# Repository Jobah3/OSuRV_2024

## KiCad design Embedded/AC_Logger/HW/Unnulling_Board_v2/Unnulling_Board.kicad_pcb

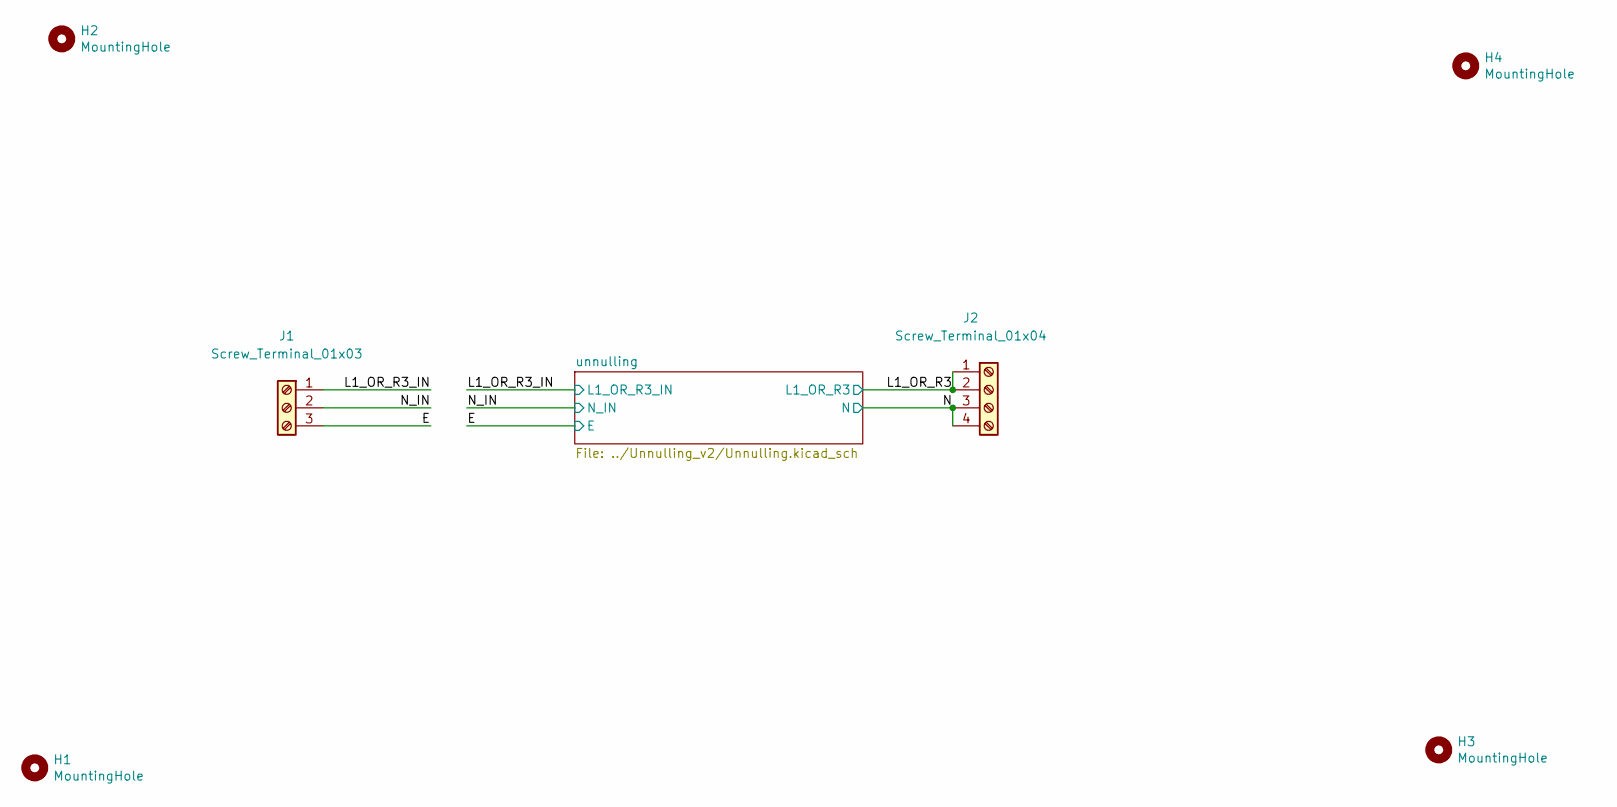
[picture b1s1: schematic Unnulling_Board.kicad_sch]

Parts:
H1, H2, H3, H4: MountingHole; MountingHole_3.2mm_M3_ISO7380_Pad
J1: Screw_Terminal_01x03; TerminalBlock_bornier-3_P5.08mm
J2: Screw_Terminal_01x04; TerminalBlock_bornier-4_P5.08mm

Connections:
/E: J1.3; also elsewhere on the board
/L1_OR_R3: J2.1, J2.2; also elsewhere on the board
/L1_OR_R3_IN: J1.1; also elsewhere on the board
/N: J2.3, J2.4; also elsewhere on the board
/N_IN: J1.2; also elsewhere on the board

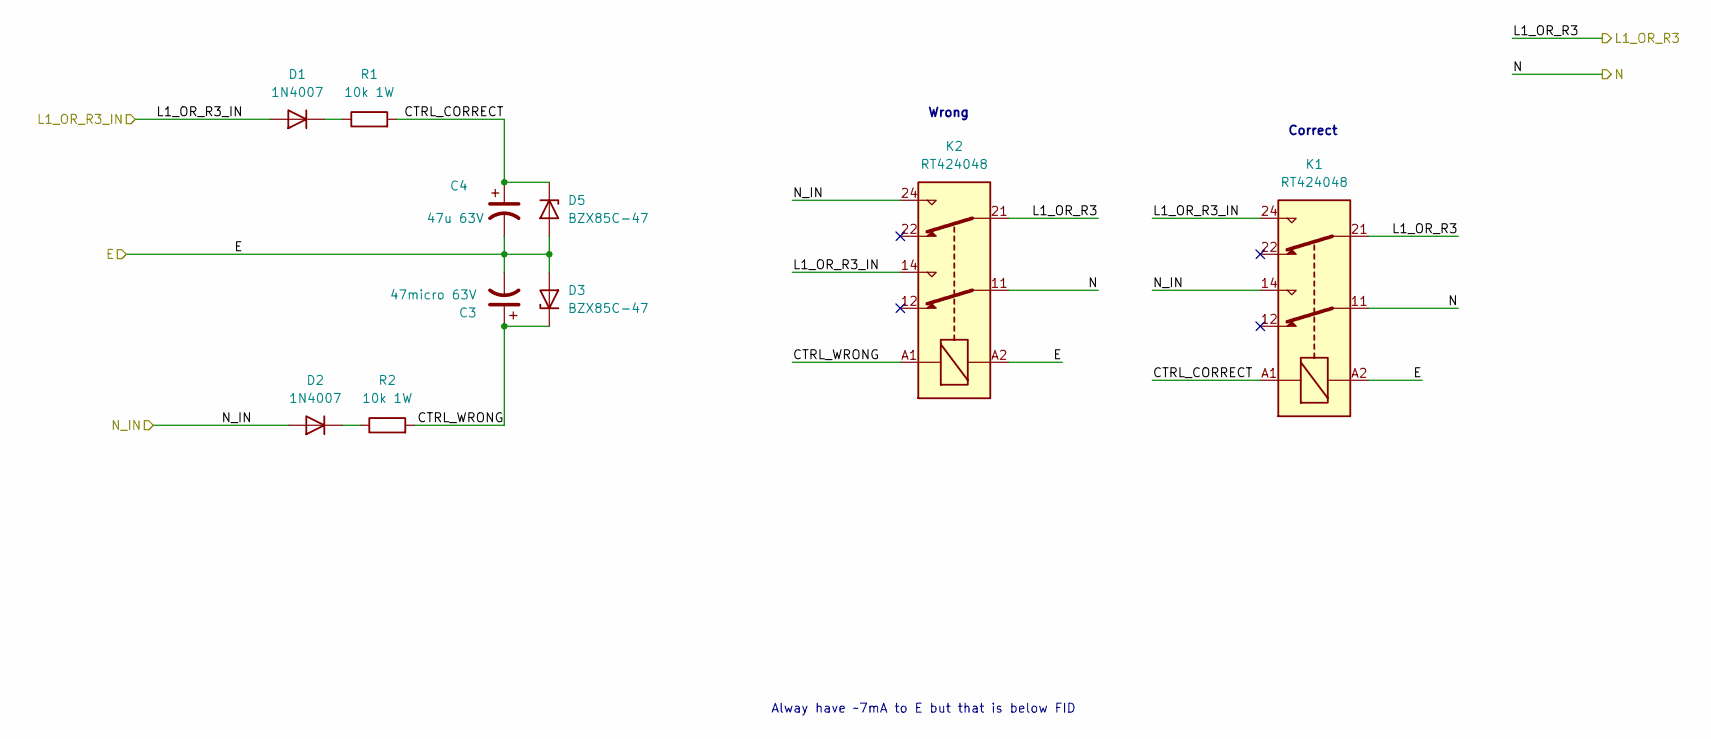
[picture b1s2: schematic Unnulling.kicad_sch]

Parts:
C3: 47micro 63V; CP_Radial_D6.3mm_P2.50mm
C4: 47u 63V; CP_Radial_D6.3mm_P2.50mm
D1, D2: 1N4007; D_DO-35_SOD27_Pinf_Horizontal
D3, D5: BZX85C-47; D_DO-41_SOD81_P2.54mm_Vertical_KathodeUp
K1, K2: RT424048; Relay_DPDT_Schrack-RT2-FormC_RM5mm
R1, R2: 10k 1W; R_Axial_DIN0309_L9.0mm_D3.2mm_P12.70mm_Horizontal

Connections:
/E: C3.2, C4.2, D3.2 (A), D5.2 (A), K1.A2, K2.A2; also elsewhere on the board
/L1_OR_R3: K1.21, K2.21; also elsewhere on the board
/L1_OR_R3_IN: D1.2 (A), K1.24, K2.14; also elsewhere on the board
/N: K1.11, K2.11; also elsewhere on the board
/N_IN: D2.2 (A), K1.14, K2.24; also elsewhere on the board
/unnulling/CTRL_CORRECT: C4.1, D5.1 (K), K1.A1, R1.2
/unnulling/CTRL_WRONG: C3.1, D3.1 (K), K2.A1, R2.2
unnamed: D1.1 (K), R1.1
unnamed: D2.1 (K), R2.1

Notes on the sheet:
Alway have ~7mA to E but that is below FID
Wrong
Correct

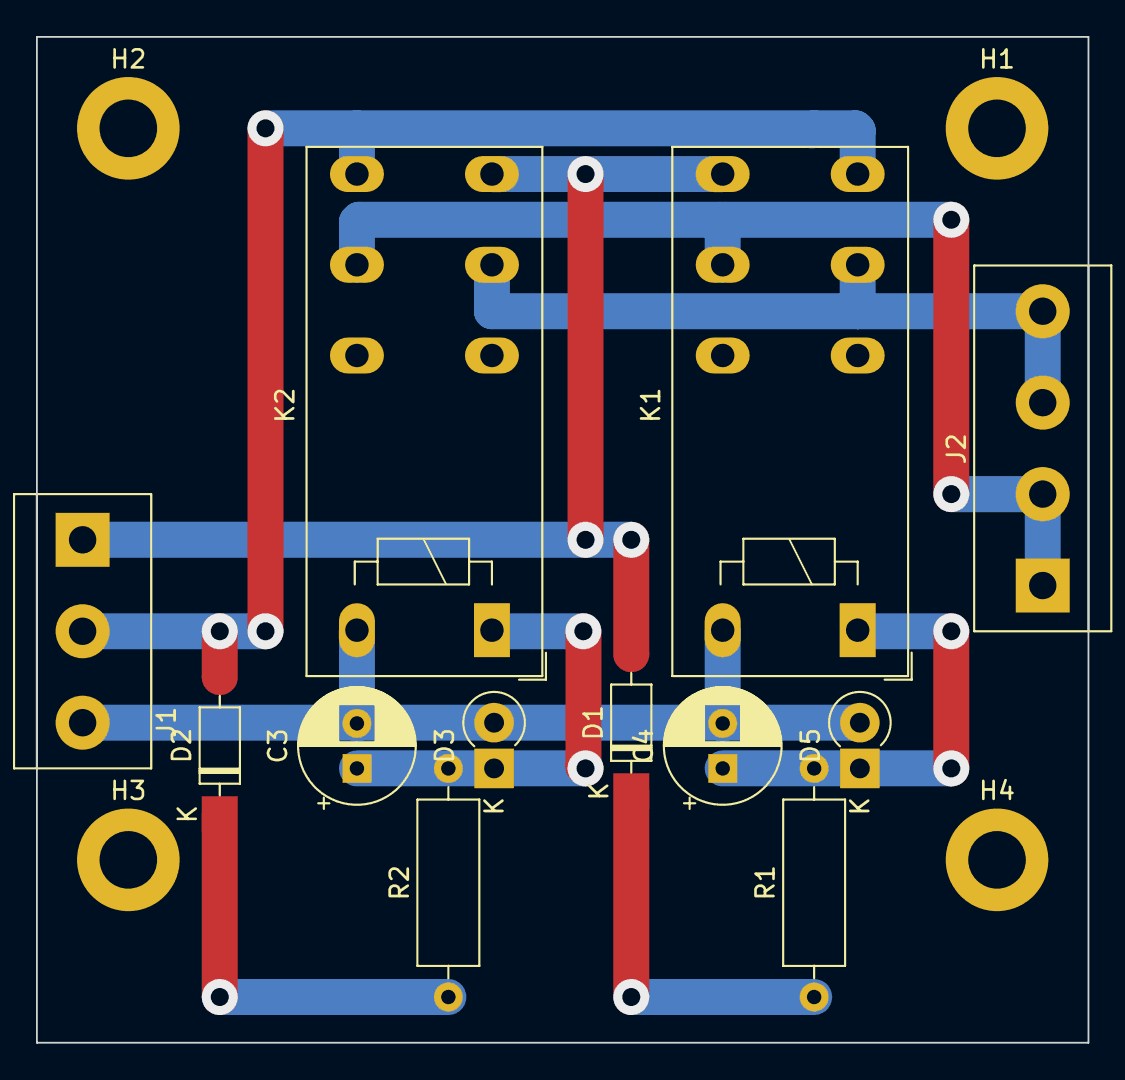
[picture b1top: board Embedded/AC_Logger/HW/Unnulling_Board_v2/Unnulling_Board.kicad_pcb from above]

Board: 2 copper layers, 58.4 x 55.9 mm, 16 parts (0 on the bottom side), 9 nets.

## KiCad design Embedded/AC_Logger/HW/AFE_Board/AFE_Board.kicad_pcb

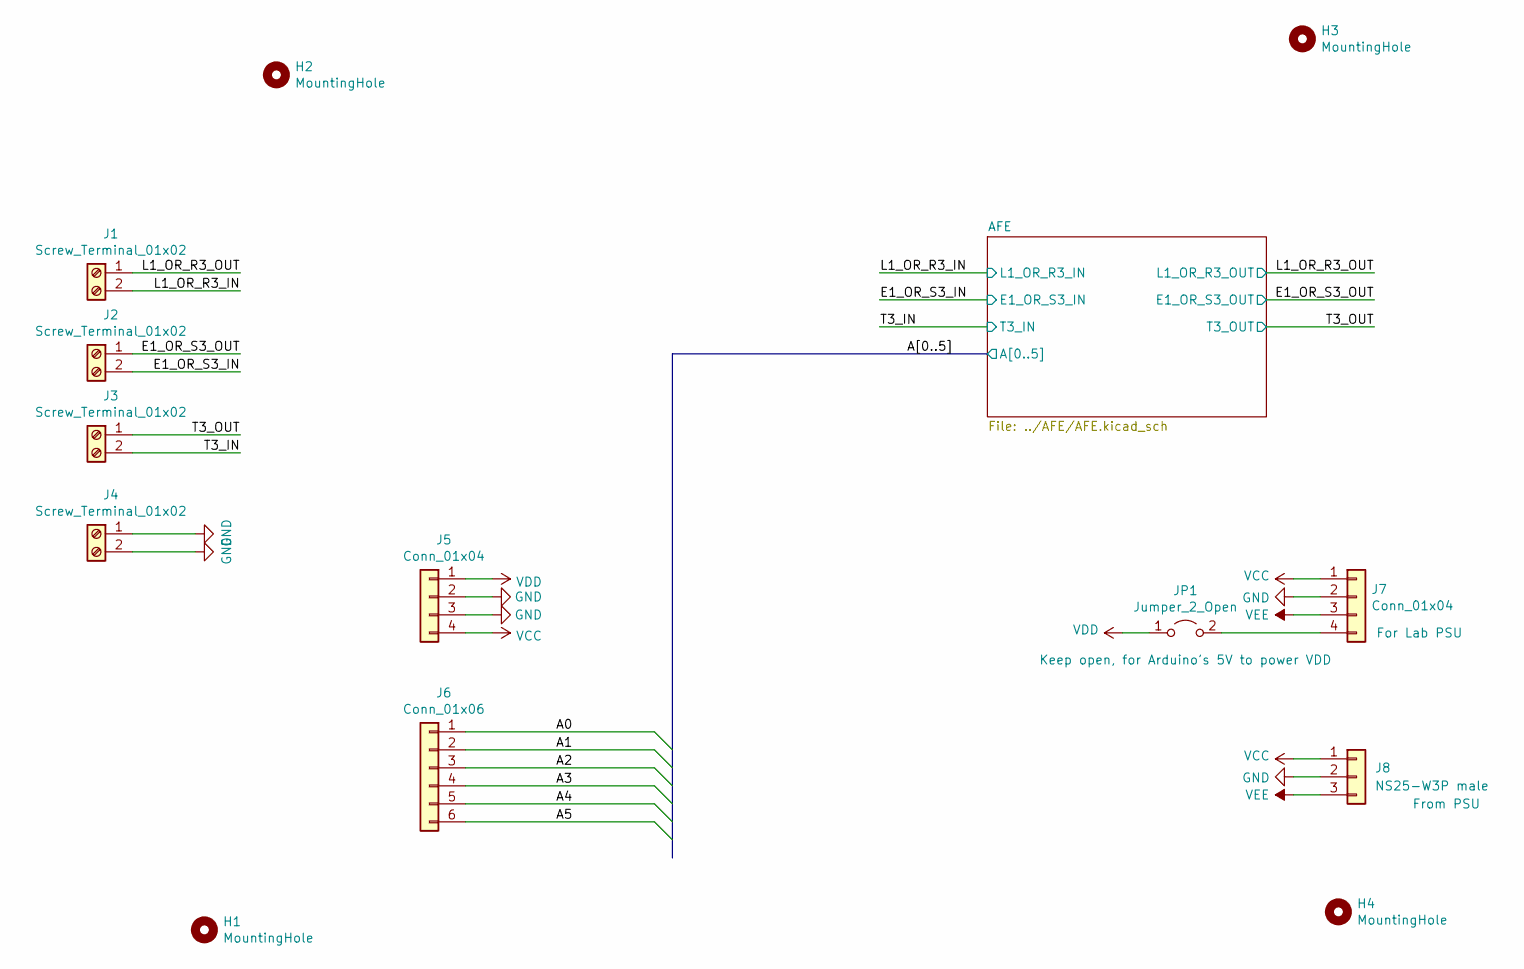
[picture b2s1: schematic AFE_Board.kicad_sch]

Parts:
H1, H2, H3, H4: MountingHole; MountingHole_3.2mm_M3_ISO7380_Pad
J1, J2, J3, J4: Screw_Terminal_01x02; TerminalBlock_bornier-2_P5.08mm
J5, J7: Conn_01x04; PinHeader_1x04_P2.54mm_Vertical
J6: Conn_01x06; PinHeader_1x06_P2.54mm_Vertical
J8: NS25-W3P male; Molex_KK-254_AE-6410-03A_1x03_P2.54mm_Vertical
JP1: Jumper_2_Open; PinHeader_1x02_P2.54mm_Vertical

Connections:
/A0: J6.1; also elsewhere on the board
/A1: J6.2; also elsewhere on the board
/A2: J6.3; also elsewhere on the board
/A3: J6.4; also elsewhere on the board
/A4: J6.5; also elsewhere on the board
/A5: J6.6; also elsewhere on the board
/E1_OR_S3_IN: J2.2; also elsewhere on the board
/E1_OR_S3_OUT: J2.1; also elsewhere on the board
/L1_OR_R3_IN: J1.2; also elsewhere on the board
/L1_OR_R3_OUT: J1.1; also elsewhere on the board
/T3_IN: J3.2; also elsewhere on the board
/T3_OUT: J3.1; also elsewhere on the board
GND: J4.1, J4.2, J5.2, J5.3, J7.2, J8.2; also elsewhere on the board
unnamed: J7.4, JP1.2 (B)
VCC: J5.4, J7.1, J8.1; also elsewhere on the board
VDD: J5.1, JP1.1 (A); also elsewhere on the board
VEE: J7.3, J8.3; also elsewhere on the board

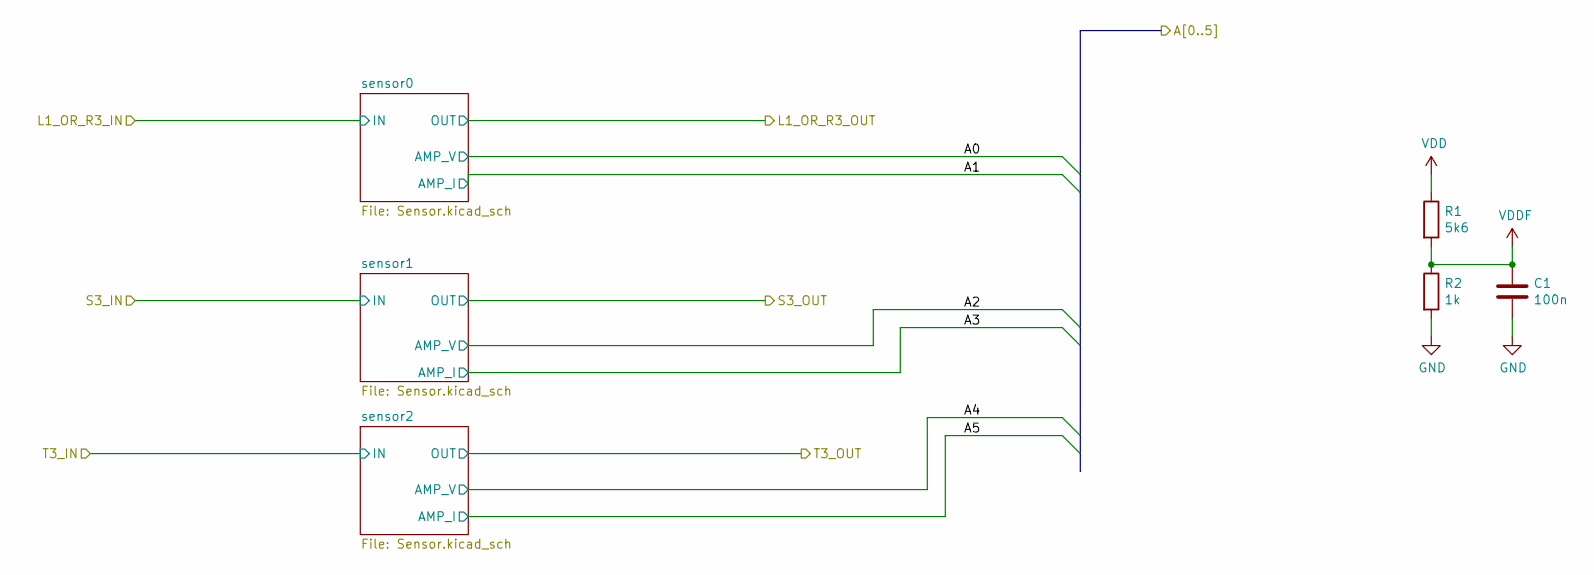
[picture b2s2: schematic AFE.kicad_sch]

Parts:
C1: 100n; C_Disc_D3.0mm_W1.6mm_Pinf
R1: 5k6; R_Axial_DIN0207_L6.3mm_D2.5mm_P2.54mm_Vertical
R2: 1k; R_Axial_DIN0207_L6.3mm_D2.5mm_Pinf_Horizontal

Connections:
GND: C1.2, R2.2; also elsewhere on the board
VDD: R1.1; also elsewhere on the board
VDDF: C1.1, R1.2, R2.1; also elsewhere on the board

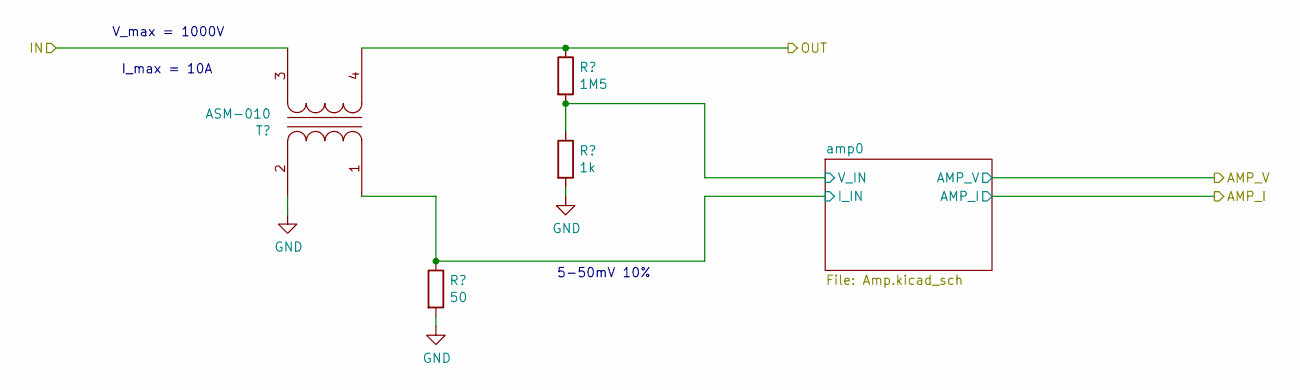
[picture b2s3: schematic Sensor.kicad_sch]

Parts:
R3: 50; R_Axial_DIN0207_L6.3mm_D2.5mm_Pinf_Horizontal
R4: 1M5; R_Axial_DIN0207_L6.3mm_D2.5mm_Pinf_Horizontal
R5: 1k; R_Axial_DIN0207_L6.3mm_D2.5mm_Pinf_Horizontal
T1: ASM-010

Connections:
/AFE/sensor0/amp0/I_IN: R3.1, T1.1 (AA); also elsewhere on the board
/AFE/sensor0/amp0/V_IN: R4.2, R5.1; also elsewhere on the board
/L1_OR_R3_IN: T1.3 (SA); also elsewhere on the board
/L1_OR_R3_OUT: R4.1, T1.4 (SB); also elsewhere on the board
GND: R3.2, R5.2, T1.2 (AB); also elsewhere on the board

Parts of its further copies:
R10, R17: 50; R_Axial_DIN0207_L6.3mm_D2.5mm_Pinf_Horizontal
R11, R18: 1M5; R_Axial_DIN0207_L6.3mm_D2.5mm_Pinf_Horizontal
R12, R19: 1k; R_Axial_DIN0207_L6.3mm_D2.5mm_Pinf_Horizontal
T2, T3: ASM-010

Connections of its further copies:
/AFE/sensor1/amp0/I_IN: R10.1, T2.1 (AA); also elsewhere on the board
/AFE/sensor1/amp0/V_IN: R11.2, R12.1; also elsewhere on the board
/AFE/sensor2/amp0/I_IN: R17.1, T3.1 (AA); also elsewhere on the board
/AFE/sensor2/amp0/V_IN: R18.2, R19.1; also elsewhere on the board
/E1_OR_S3_IN: T2.3 (SA); also elsewhere on the board
/E1_OR_S3_OUT: R11.1, T2.4 (SB); also elsewhere on the board
/T3_IN: T3.3 (SA); also elsewhere on the board
/T3_OUT: R18.1, T3.4 (SB); also elsewhere on the board
GND: R10.2, R12.2, R17.2, R19.2, T2.2 (AB), T3.2 (AB); also elsewhere on the board

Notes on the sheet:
V_max = 1000V
5-50mV 10%
I_max = 10A

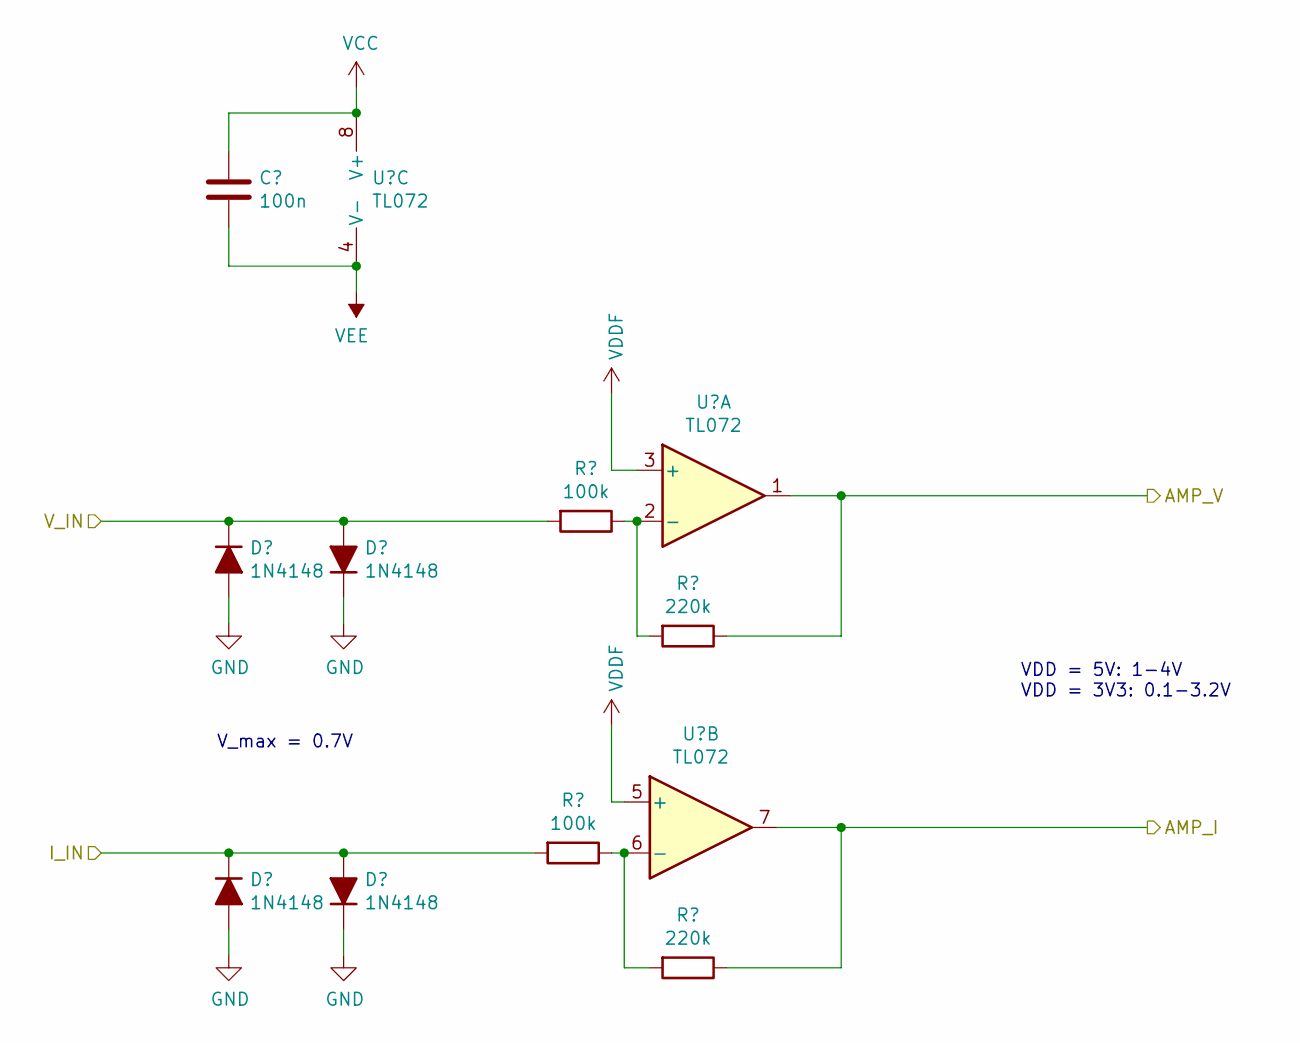
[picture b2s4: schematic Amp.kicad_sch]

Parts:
C2: 100n; C_Disc_D3.0mm_W1.6mm_Pinf
D1, D2, D3, D4: 1N4148; R_Axial_DIN0207_L6.3mm_D2.5mm_Pinf_Horizontal
R6, R7: 100k; R_Axial_DIN0207_L6.3mm_D2.5mm_Pinf_Horizontal
R8, R9: 220k; R_Axial_DIN0207_L6.3mm_D2.5mm_P2.54mm_Vertical
U1: TL072; DIP-8_W7.62mm

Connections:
/A0: R8.1, U1.1; also elsewhere on the board
/A1: R9.1, U1.7; also elsewhere on the board
/AFE/sensor0/amp0/I_IN: D2.1 (K), D4.2 (A), R6.2; also elsewhere on the board
/AFE/sensor0/amp0/V_IN: D1.1 (K), D3.2 (A), R7.2; also elsewhere on the board
GND: D1.2 (A), D2.2 (A), D3.1 (K), D4.1 (K); also elsewhere on the board
unnamed: R6.1, R9.2, U1.6 (-)
unnamed: R7.1, R8.2, U1.2 (-)
VCC: C2.1, U1.8 (V+); also elsewhere on the board
VDDF: U1.3 (+), U1.5 (+); also elsewhere on the board
VEE: C2.2, U1.4 (V-); also elsewhere on the board

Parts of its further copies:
C3, C4: 100n; C_Disc_D3.0mm_W1.6mm_Pinf
D5, D6, D7, D8, D9, D10, D11, D12: 1N4148; R_Axial_DIN0207_L6.3mm_D2.5mm_Pinf_Horizontal
R13, R14, R20, R21: 100k; R_Axial_DIN0207_L6.3mm_D2.5mm_Pinf_Horizontal
R15, R16, R22, R23: 220k; R_Axial_DIN0207_L6.3mm_D2.5mm_P2.54mm_Vertical
U2, U3: TL072; DIP-8_W7.62mm

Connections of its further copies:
/A2: R15.1, U2.1; also elsewhere on the board
/A3: R16.1, U2.7; also elsewhere on the board
/A4: R22.1, U3.1; also elsewhere on the board
/A5: R23.1, U3.7; also elsewhere on the board
/AFE/sensor1/amp0/I_IN: D6.1 (K), D8.2 (A), R13.2; also elsewhere on the board
/AFE/sensor1/amp0/V_IN: D5.1 (K), D7.2 (A), R14.2; also elsewhere on the board
/AFE/sensor2/amp0/I_IN: D10.1 (K), D12.2 (A), R20.2; also elsewhere on the board
/AFE/sensor2/amp0/V_IN: D9.1 (K), D11.2 (A), R21.2; also elsewhere on the board
GND: D5.2 (A), D6.2 (A), D7.1 (K), D8.1 (K), D9.2 (A), D10.2 (A), D11.1 (K), D12.1 (K); also elsewhere on the board
unnamed: R13.1, R16.2, U2.6 (-)
unnamed: R14.1, R15.2, U2.2 (-)
unnamed: R20.1, R23.2, U3.6 (-)
unnamed: R21.1, R22.2, U3.2 (-)
VCC: C3.1, C4.1, U2.8 (V+), U3.8 (V+); also elsewhere on the board
VDDF: U2.3 (+), U2.5 (+), U3.3 (+), U3.5 (+); also elsewhere on the board
VEE: C3.2, C4.2, U2.4 (V-), U3.4 (V-); also elsewhere on the board

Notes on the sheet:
V_max = 0.7V
VDD = 5V: 1-4V VDD = 3V3: 0.1-3.2V

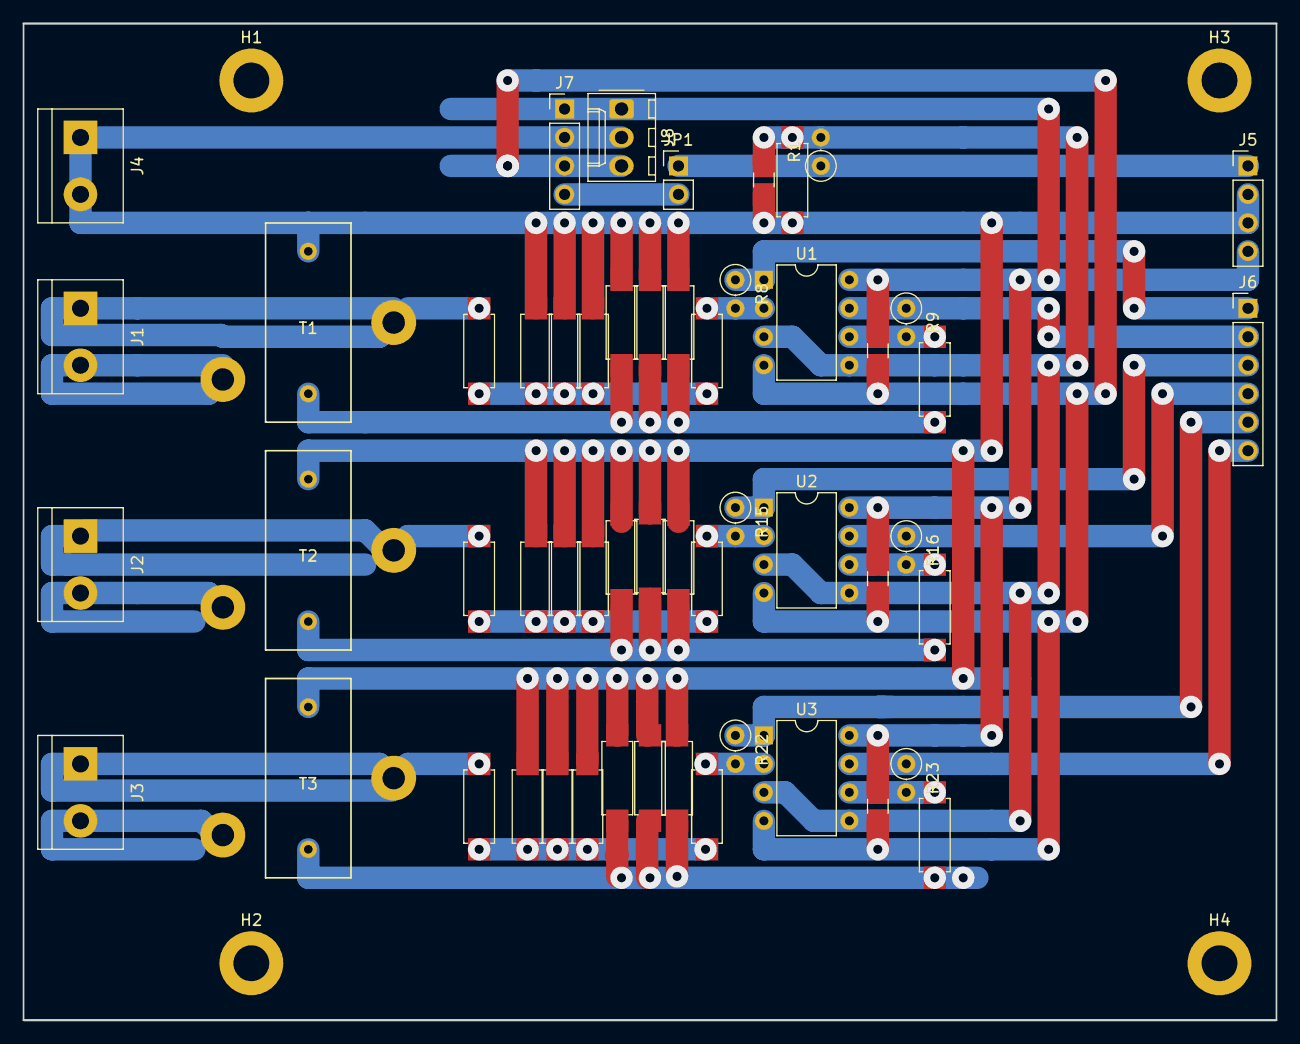
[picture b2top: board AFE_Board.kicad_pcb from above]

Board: 2 copper layers, 111.8 x 88.9 mm, 58 parts (0 on the bottom side), 30 nets.

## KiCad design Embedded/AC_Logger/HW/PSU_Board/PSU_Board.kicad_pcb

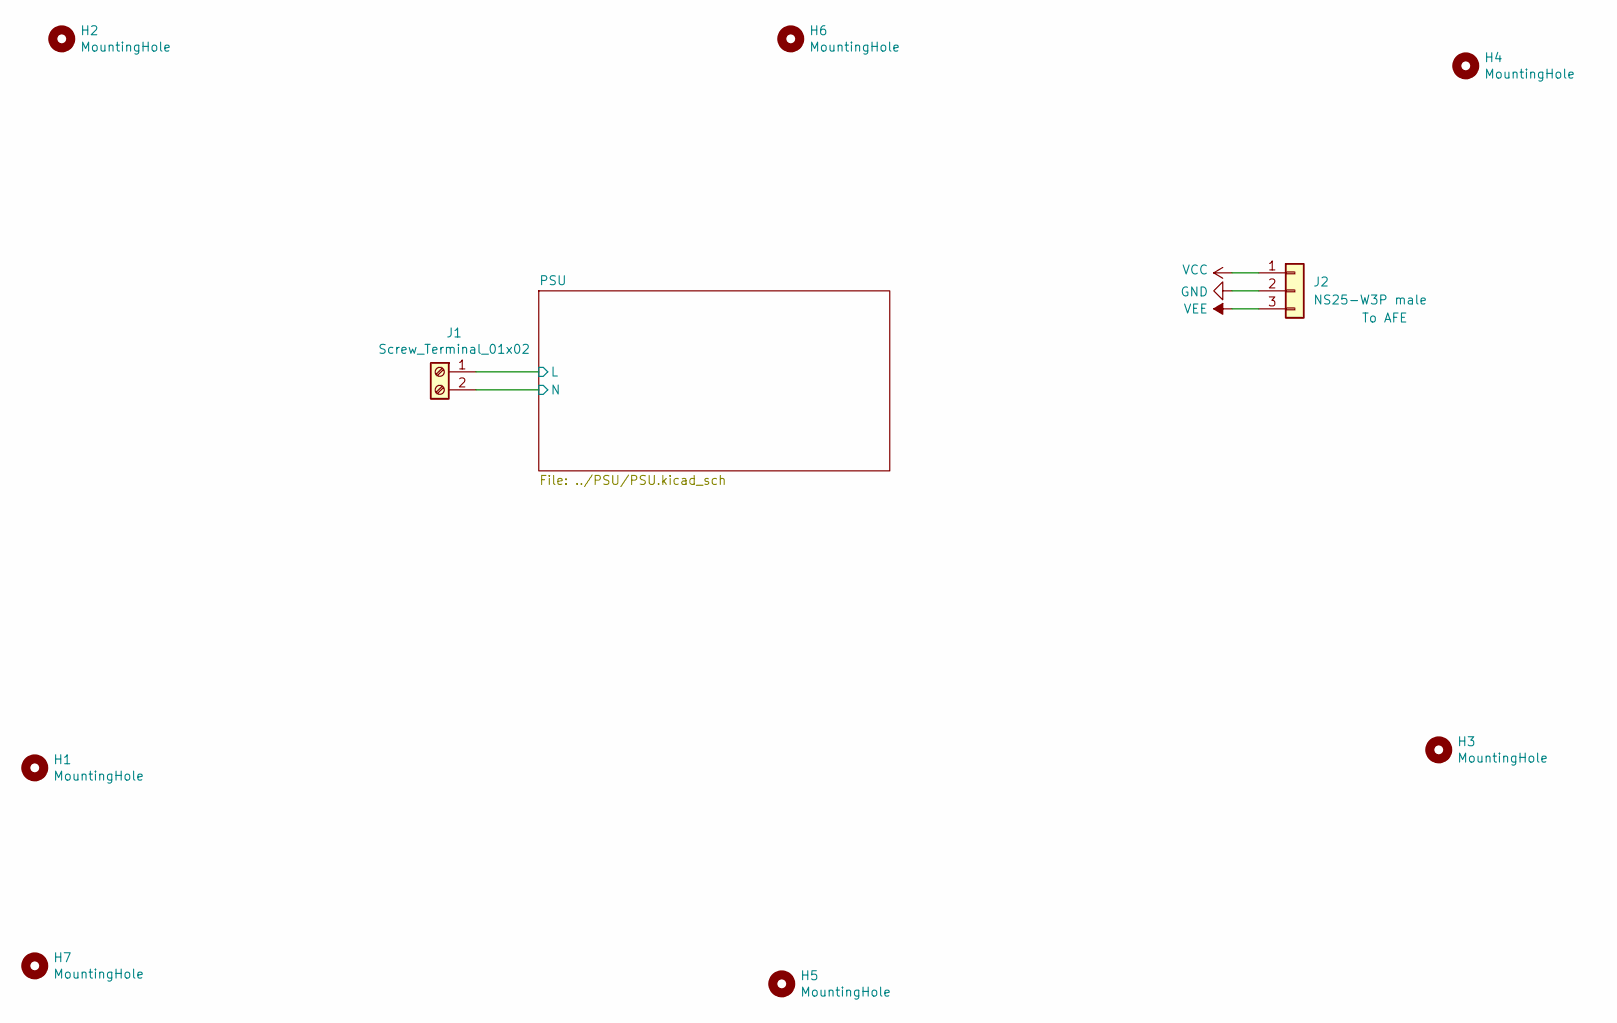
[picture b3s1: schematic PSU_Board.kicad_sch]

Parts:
H1, H2, H3, H4, H5, H6, H7: MountingHole; MountingHole_3.2mm_M3_ISO7380_Pad
J1: Screw_Terminal_01x02; TerminalBlock_bornier-2_P5.08mm
J2: NS25-W3P male; Molex_KK-254_AE-6410-03A_1x03_P2.54mm_Vertical

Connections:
/PSU/L: J1.1; also elsewhere on the board
/PSU/N: J1.2; also elsewhere on the board
GND: J2.2; also elsewhere on the board
VCC: J2.1; also elsewhere on the board
VEE: J2.3; also elsewhere on the board

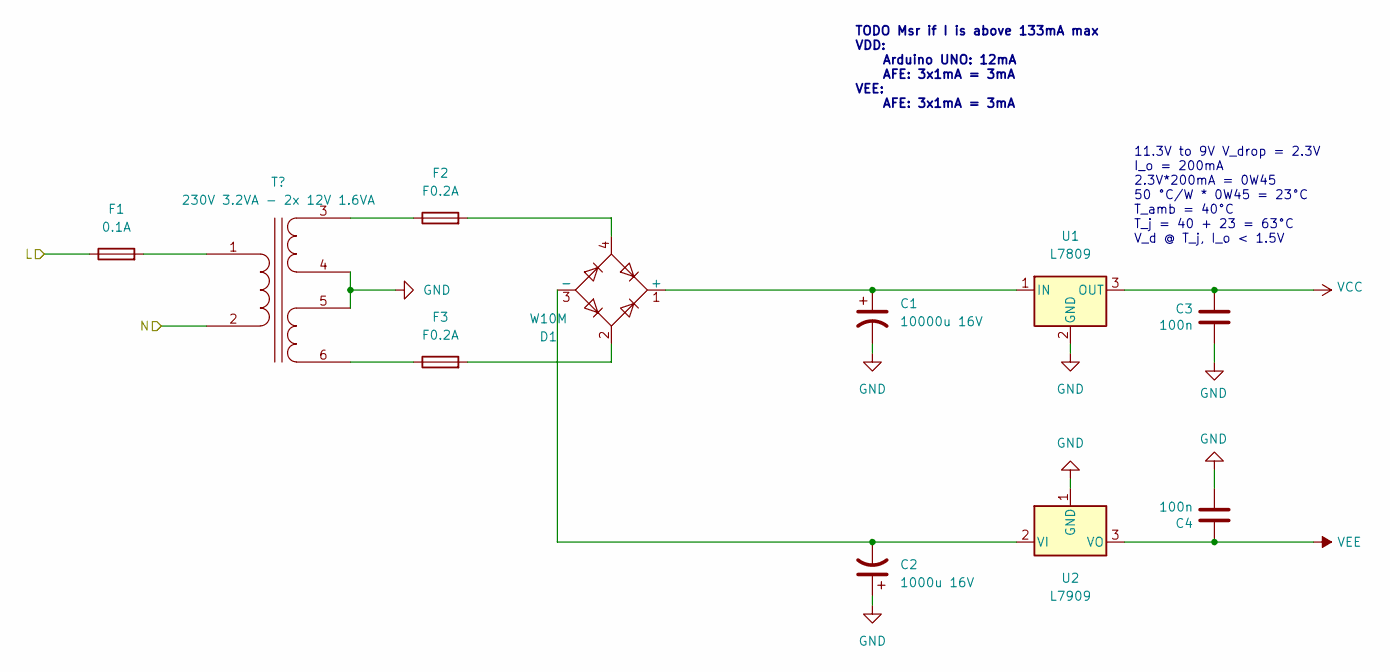
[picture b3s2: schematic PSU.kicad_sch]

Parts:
C1: 10000u 16V; CP_Radial_D16.0mm_P7.50mm
C2: 1000u 16V; CP_Radial_D10.0mm_P5.00mm
C3, C4: 100n; C_Disc_D3.0mm_W1.6mm_P2.50mm
D1: W10M; Diode_Bridge_Round_D9.8mm
F1: 0.1A; Fuseholder_Clip-5x20mm_Littelfuse_111_Inline_P20.00x5.00mm_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
F2, F3: F0.2A; Fuseholder_Clip-5x20mm_Littelfuse_111_Inline_P20.00x5.00mm_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
T1: 230V 3.2VA - 2x 12V 1.6VA; Transformer-3VA_2xSec
U1: L7809; TO-220-3_Vertical
U2: L7909; TO-220-3_Vertical

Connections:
/PSU/L: F1.1; also elsewhere on the board
/PSU/N: T1.2 (AB); also elsewhere on the board
GND: C1.2, C2.1, C3.2, C4.2, T1.4 (SB), T1.5 (SC), U1.2 (GND), U2.1 (GND); also elsewhere on the board
unnamed: C1.1, D1.1 (+), U1.1 (IN)
unnamed: C2.2, D1.3 (-), U2.2 (VI)
unnamed: D1.2, F3.2
unnamed: D1.4, F2.2
unnamed: F1.2, T1.1 (AA)
unnamed: F2.1, T1.3 (SA)
unnamed: F3.1, T1.6 (SD)
VCC: C3.1, U1.3 (OUT); also elsewhere on the board
VEE: C4.1, U2.3 (VO); also elsewhere on the board

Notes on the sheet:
TODO Msr if I is above 133mA max VDD: Arduino UNO: 12mA AFE: 3x1mA = 3mA VEE: AFE: 3x1mA = 3mA
11.3V to 9V V_drop = 2.3V I_o = 200mA 2.3V*200mA = 0W45 50 °C/W * 0W45 = 23°C T_amb = 40°C T_j = 40 + 23 = 63°C V_d @ T_j, I_o < 1.5V

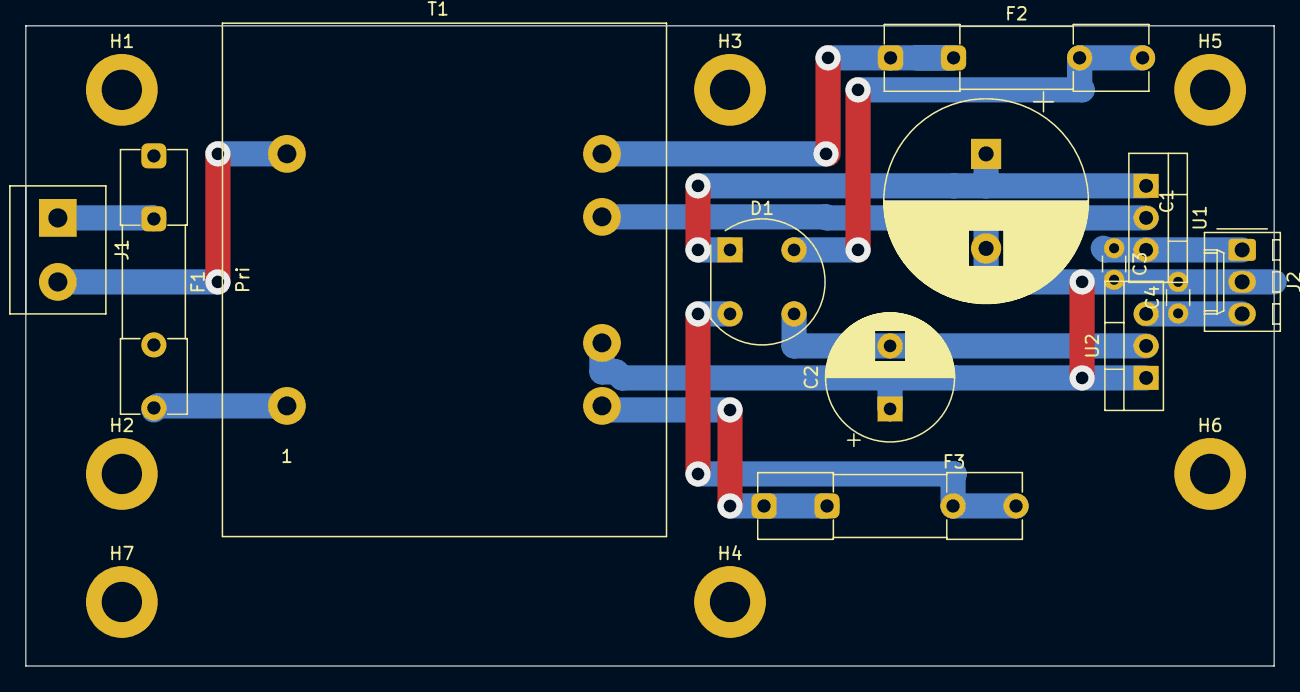
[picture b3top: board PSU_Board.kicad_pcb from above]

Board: 2 copper layers, 99.1 x 50.8 mm, 20 parts (0 on the bottom side), 12 nets.

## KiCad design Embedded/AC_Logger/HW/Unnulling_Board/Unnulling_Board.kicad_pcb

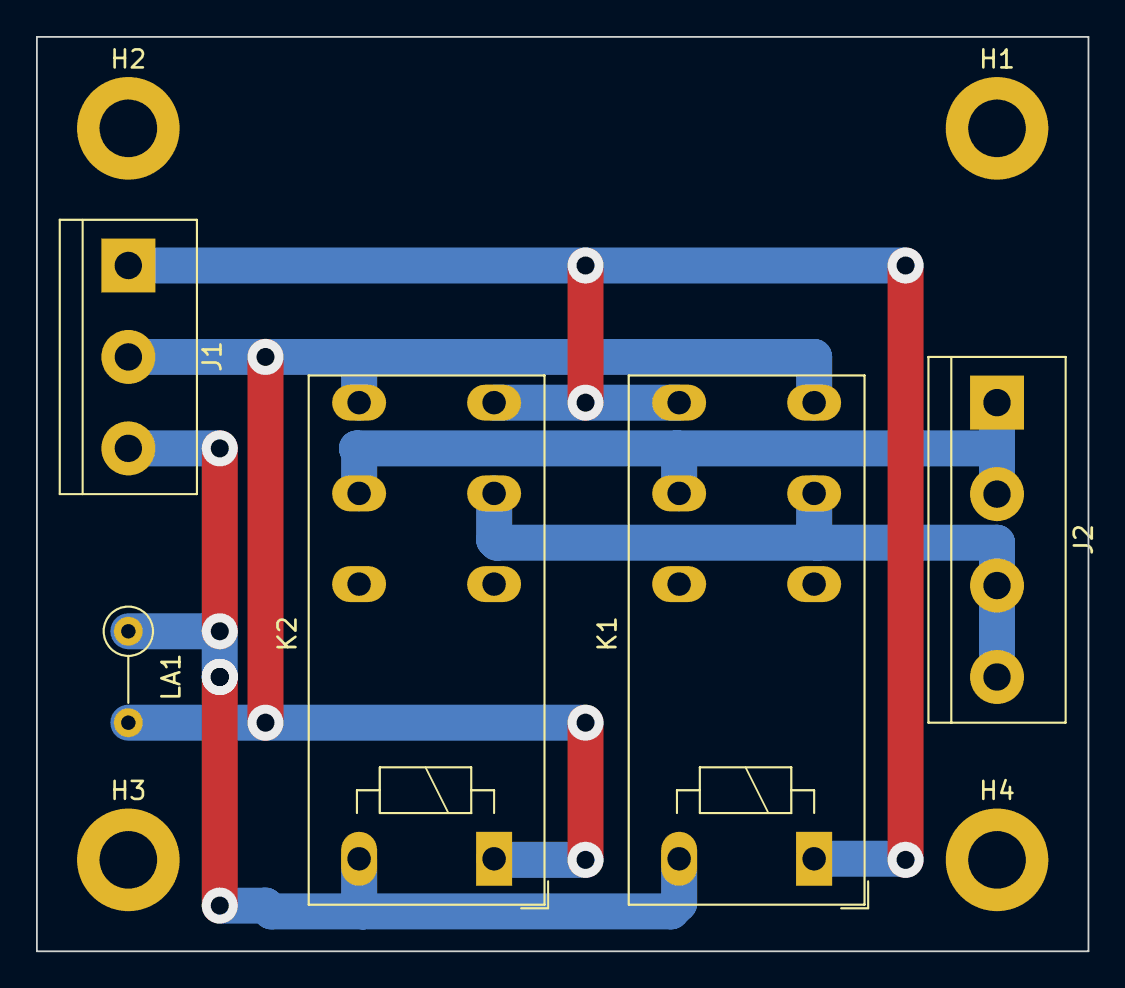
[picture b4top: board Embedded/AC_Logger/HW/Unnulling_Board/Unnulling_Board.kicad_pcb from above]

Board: 2 copper layers, 58.4 x 50.8 mm, 9 parts (0 on the bottom side), 5 nets.

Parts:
H1, H2, H3, H4: MountingHole; MountingHole_3.2mm_M3_ISO7380_Pad
J1: Screw_Terminal_01x03; TerminalBlock_bornier-3_P5.08mm
J2: Screw_Terminal_01x04; TerminalBlock_bornier-4_P5.08mm
K1, K2: RT424730; Relay_DPDT_Schrack-RT2-FormC_RM5mm
LA1: Lamp; R_Axial_DIN0207_L6.3mm_D2.5mm_P5.08mm_Vertical

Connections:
/E: J1.3, K1.A2, K2.A2, LA1.1 (-)
/L1_OR_R3: J2.1, J2.2, K1.21, K2.21
/L1_OR_R3_IN: J1.1, K1.24, K1.A1, K2.14
/N: J2.3, J2.4, K1.11, K2.11
/N_IN: J1.2, K1.14, K2.24, K2.A1, LA1.2 (+)

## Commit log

2025-07-23 PCB changed to make sandwitch.
2025-07-24 Tasks.
2025-07-24 Not needed.
2025-07-24 Also not needed.
2025-08-27 Corrections.
2025-08-29 Correction.
2025-08-29 FW corrected.
2025-08-29 BOM for new board.
2025-08-29 TODOs.
2025-09-30 New PCB.
2025-09-30 Final v2
2025-10-07 Nothing.
2025-10-07 Doc.
